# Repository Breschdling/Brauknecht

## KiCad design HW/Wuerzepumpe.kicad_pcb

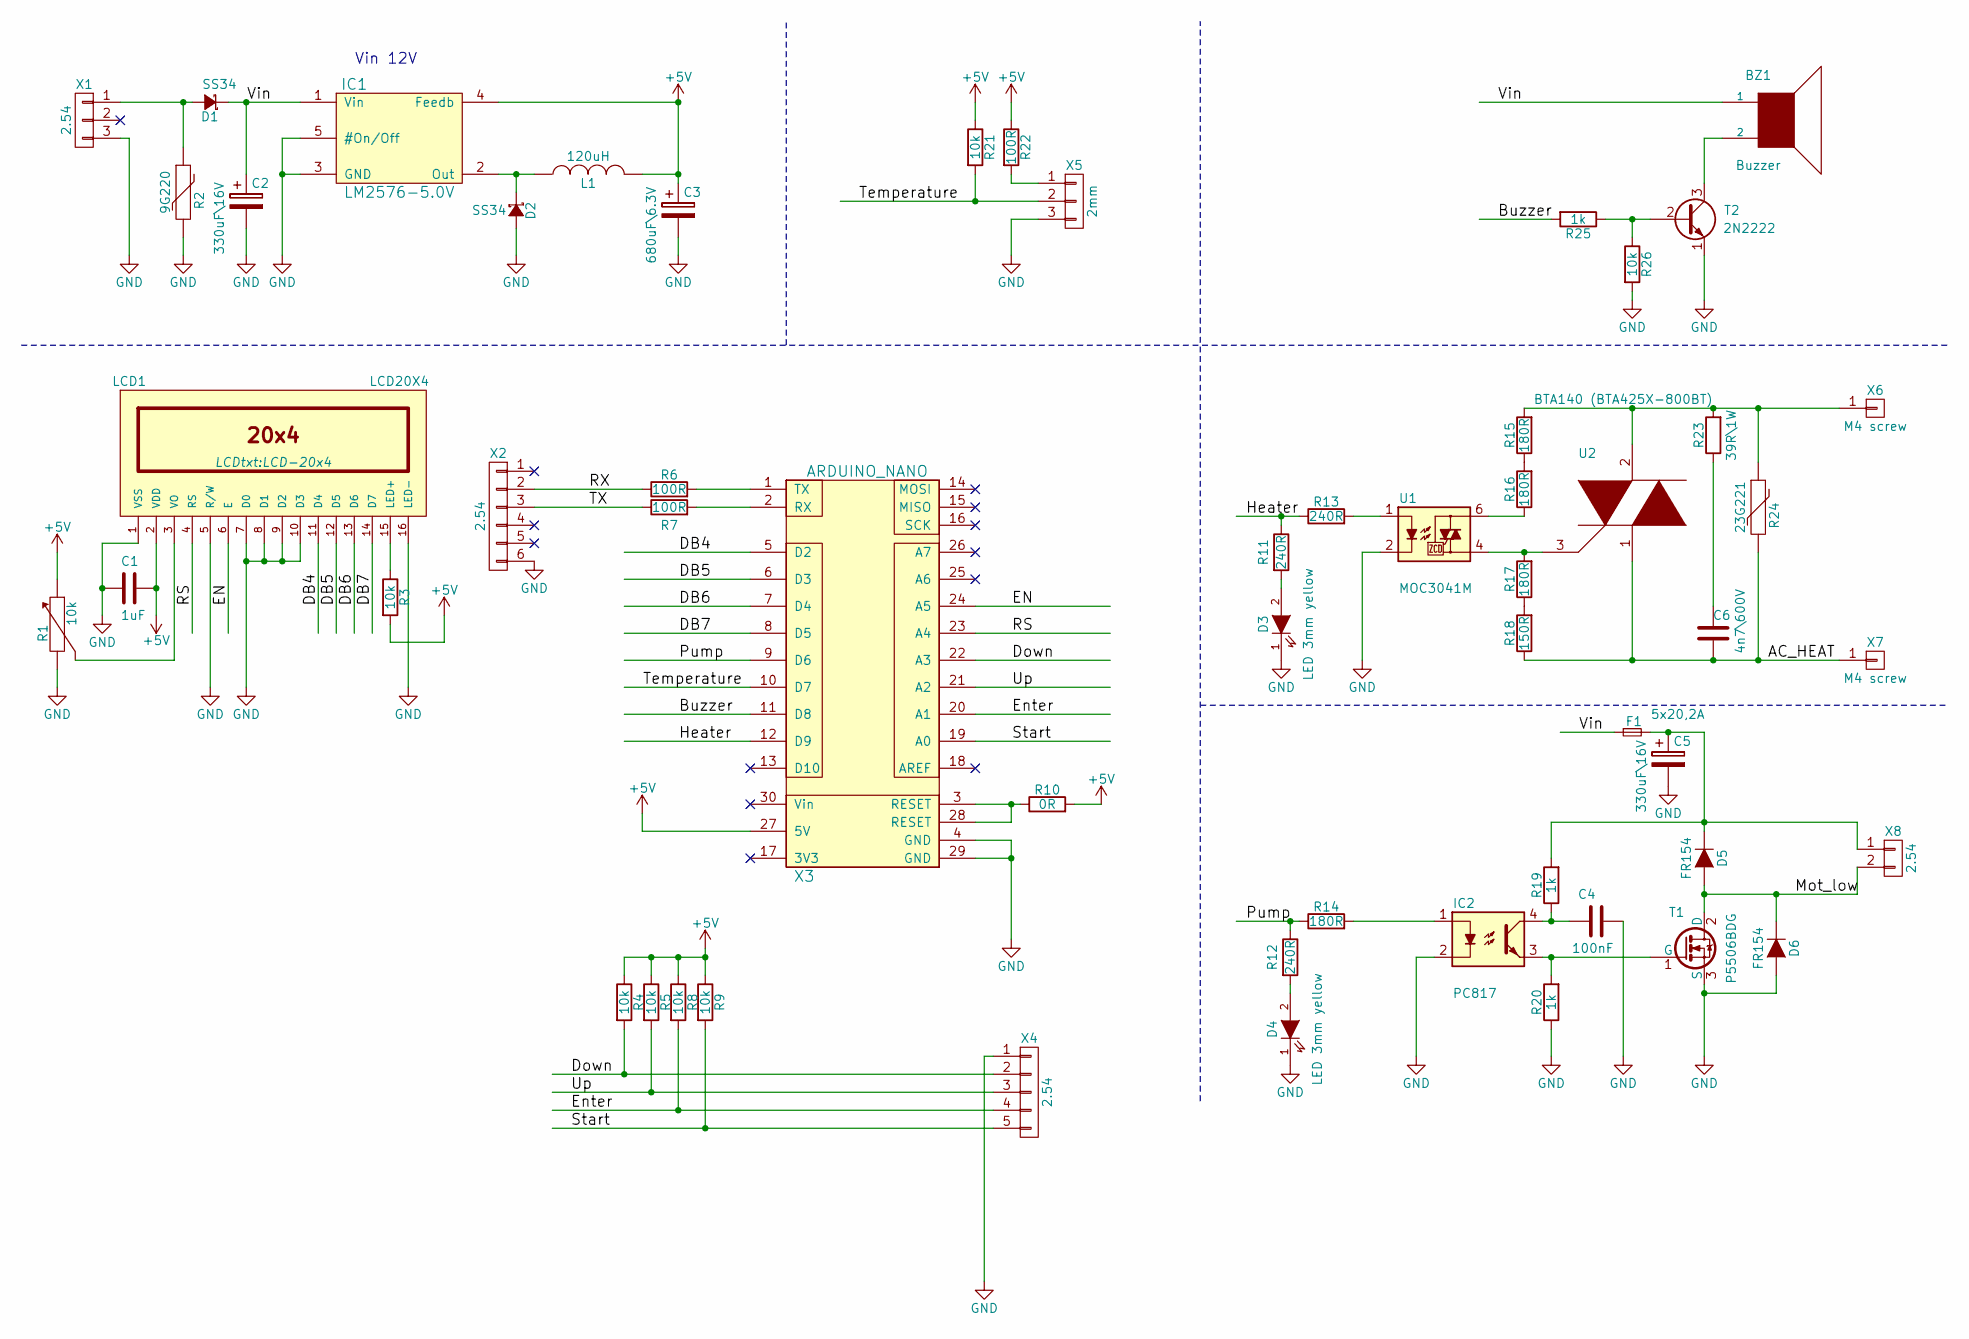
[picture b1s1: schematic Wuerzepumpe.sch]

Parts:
BZ1: Buzzer; Buzzer_13.8x7.5RM7.6
C1: 1uF; C_0805_HandSoldering
C2, C5: 330uF\\16V; CP_Radial_D10.0mm_P5.00mm_P7.50mm
C3: 680uF\\6.3V; CP_Radial_D10.0mm_P5.00mm_P7.50mm
C4: 100nF; C_0805_HandSoldering
C6: 4n7\\600V; C_Disc_D8.0mm_W5.0mm_P7.50mm
D1, D2: SS34; D_SMA_Handsoldering
D3, D4: LED 3mm yellow; LED_D3.0mm
D5, D6: FR154; D_DO-15_P2.54mm_Vertical_AnodeUp
F1: 5x20,2A; Fuseholder5x20_horiz_open_Schurter_0031_8201
IC1: LM2576-5.0V; TO-263-5Lead
IC2: PC817; DIP-4_W7.62mm_LongPads
L1: 120uH; 16mm_Radial
LCD1: LCD20X4; LCD-20x4
R1: 10k; GF063P1-3
R2: 9G220; RV_Disc_D9_W3.4_P5
R3, R4, R5, R8, R9, R21, R26: 10k; R_0805_HandSoldering
R6, R7, R22: 100R; R_0805_HandSoldering
R10: 0R; R_0805_HandSoldering
R11, R12, R13: 240R; R_0805_HandSoldering
R14, R15, R16, R17: 180R; R_0805_HandSoldering
R18: 150R; R_0805_HandSoldering
R19, R20, R25: 1k; R_0805_HandSoldering
R23: 39R\\1W; R_Axial_DIN0204_L3.6mm_D1.6mm_P2.54mm_Vertical
R24: 23G221; RV_Disc_D15.5_W3.9_P7.5
T1: P5506BDG; TO-252-2Lead
T2: 2N2222; TO-92_Inline_Narrow_Oval
U1: MOC3041M; DIP-6_W7.62mm
U2: BTA140 (BTA425X-800BT); TO-220_Neutral123_Vertical_LargePads
X1: 2.54; Molex_KK-6410-03_03x2.54mm_Straight
X2: 2.54; Pin_Header_Straight_1x06_Pitch2.54mm
X3: ARDUINO_NANO; arduino_nano
X4: 2.54; Pin_Header_Straight_1x05_Pitch2.54mm
X5: 2mm; Molex_MicroLatch-53253-0370_03x2.00mm_Straight
X6, X7: M4 screw; GD-G13
X8: 2.54; Molex_KK-6410-02_02x2.54mm_Straight

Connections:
+5V: C1.1, C3.1, IC1.4 (Feedb), L1.2, LCD1.2 (VDD), R1.1, R3.2, R4.1, R5.1, R8.1, R9.1, R10.2, R21.1, R22.1, X3.27 (5V)
/AC_HEAT: C6.1, R18.1, R24.2, U2.1, X7.1
/Buzzer: R25.2, X3.11 (D8)
/DB4: LCD1.11 (D4), X3.5 (D2)
/DB5: LCD1.12 (D5), X3.6 (D3)
/DB6: LCD1.13 (D6), X3.7 (D4)
/DB7: LCD1.14 (D7), X3.8 (D5)
/Down: R4.2, X3.22 (A3), X4.2
/EN: LCD1.6 (E), X3.24 (A5)
/Enter: R8.2, X3.20 (A1), X4.4
/Heater: R11.1, R13.1, X3.12 (D9)
/Mot_low: D5.2 (A), D6.1 (K), T1.2 (D), X8.2
/Pump: R12.1, R14.1, X3.9 (D6)
/RS: LCD1.4 (RS), X3.23 (A4)
/RX: R6.1, X2.2
/Start: R9.2, X3.19 (A0), X4.5
/TX: R7.1, X2.3
/Temperature: R21.2, X3.10 (D7), X5.2
/Up: R5.2, X3.21 (A2), X4.3
/Vin: BZ1.1, C2.1, D1.1 (K), F1.1, IC1.1 (Vin)
GND: C1.2, C2.2, C3.2, C4.2, C5.2, D2.2 (A), D3.1 (K), D4.1 (K), D6.2 (A), IC1.3 (GND), IC1.5 (#On/Off), IC2.2, LCD1.1 (VSS), LCD1.5 (R/W), LCD1.7 (D0), LCD1.8 (D1), LCD1.9 (D2), LCD1.10 (D3), LCD1.16 (LED-), R1.3, R2.2, R20.1, R26.2, T1.3 (S), T2.1 (E), U1.2, X1.3, X2.6, X3.4 (GND), X3.29 (GND), X4.1, X5.3
unnamed: BZ1.2, T2.3 (C)
unnamed: C4.1, IC2.4, R19.1
unnamed: C5.1, D5.1 (K), F1.2, R19.2, X8.1
unnamed: C6.2, R23.1
unnamed: D1.2 (A), R2.1, X1.1
unnamed: D2.1 (K), IC1.2 (Out), L1.1
unnamed: D3.2 (A), R11.2
unnamed: D4.2 (A), R12.2
unnamed: IC2.1, R14.2
unnamed: IC2.3, R20.2, T1.1 (G)
unnamed: LCD1.3 (VO), R1.2
unnamed: LCD1.15 (LED+), R3.1
unnamed: R6.2, X3.1 (TX)
unnamed: R7.2, X3.2 (RX)
unnamed: R10.1, X3.3 (RESET), X3.28 (RESET)
unnamed: R13.2, U1.1
unnamed: R15.1, R16.2
unnamed: R15.2, R23.2, R24.1, U2.2, X6.1
unnamed: R16.1, U1.6
unnamed: R17.1, R18.2
unnamed: R17.2, U1.4, U2.3
unnamed: R22.2, X5.1
unnamed: R25.1, R26.1, T2.2 (B)

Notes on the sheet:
Vin 12V

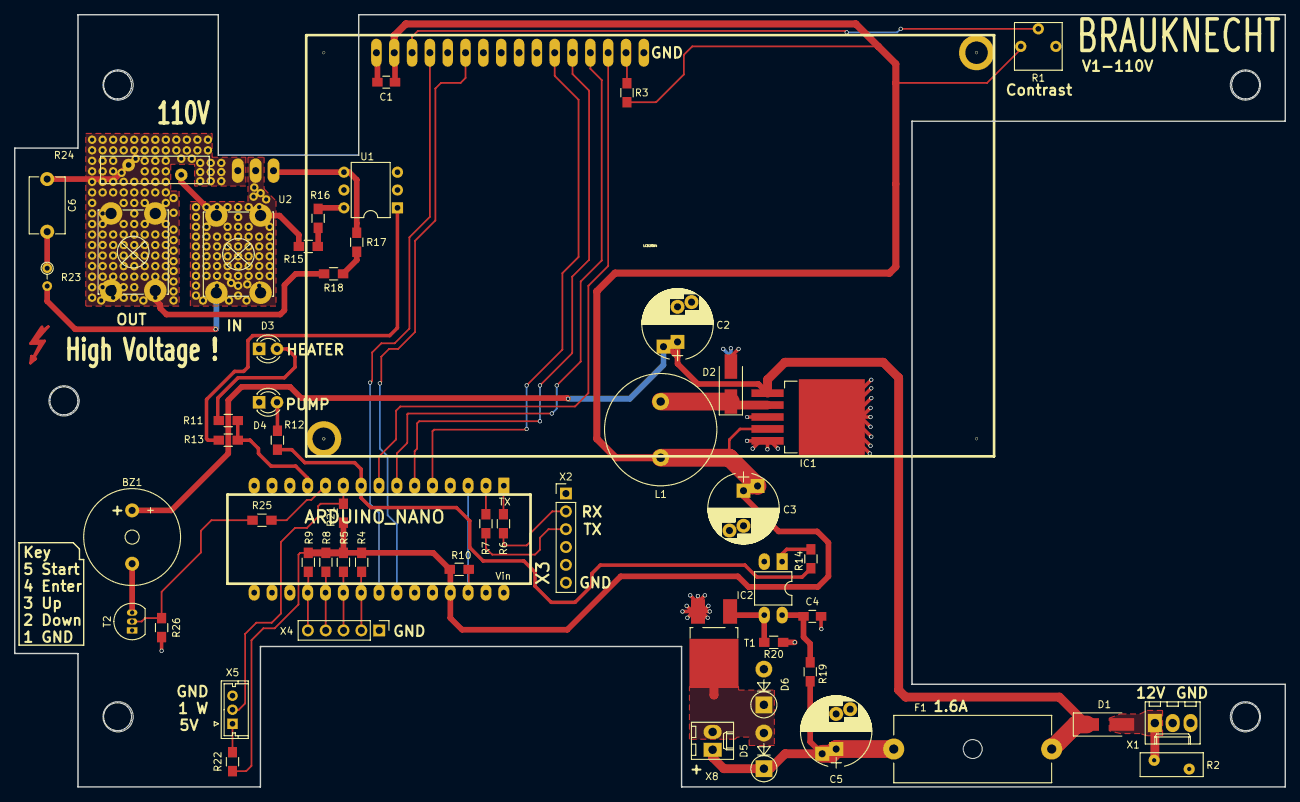
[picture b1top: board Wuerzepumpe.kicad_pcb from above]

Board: 2 copper layers, 181.0 x 110.0 mm, 55 parts (1 on the bottom side), 36 nets.

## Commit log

2023-01-19 Initial upload
